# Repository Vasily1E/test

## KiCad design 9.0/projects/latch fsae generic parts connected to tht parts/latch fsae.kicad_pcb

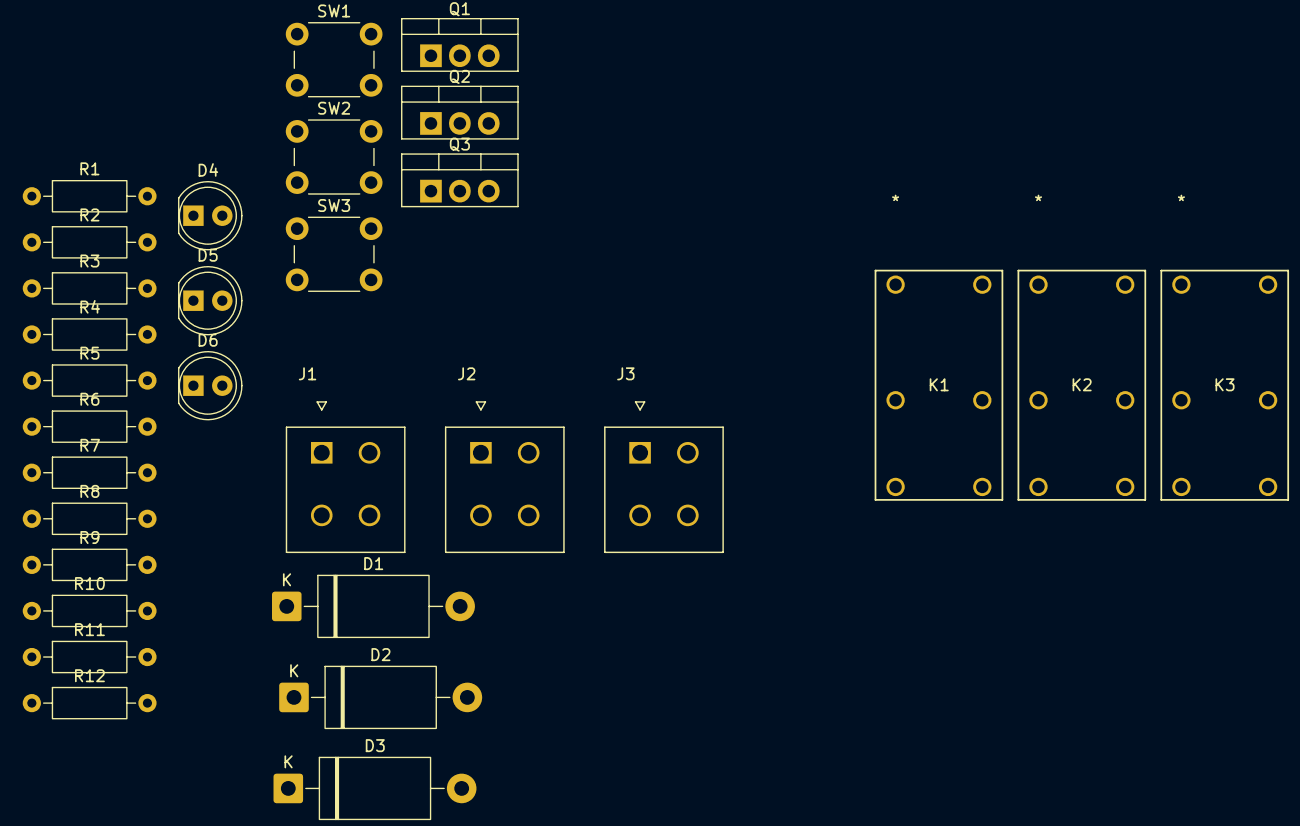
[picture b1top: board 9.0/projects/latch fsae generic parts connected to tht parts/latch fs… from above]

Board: 2 copper layers, 30 parts (0 on the bottom side), 20 nets, no tracks yet.

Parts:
D1, D2, D3: 1N4148WT; D_DO-201_P15.24mm_Horizontal
D4, D5, D6: DEBUG LED; LED_D5.0mm
J1, J2, J3: 2x2con; MOLEX_39296048
K1, K2, K3: Relay_DPST-NO; RELAY_G6B-2114P-US_OMR
Q1, Q2, Q3: PMOS; TO-220-3_Vertical
R1, R2, R3, R6, R8, R11: 1k; R_Axial_DIN0207_L6.3mm_D2.5mm_P10.16mm_Horizontal
R4, R7, R9: 470; R_Axial_DIN0207_L6.3mm_D2.5mm_P10.16mm_Horizontal
R5, R10, R12: 10k; R_Axial_DIN0207_L6.3mm_D2.5mm_P10.16mm_Horizontal
SW1, SW2, SW3: SW_Push; SW_PUSH_6mm

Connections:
+12V: J1.2, Q1.3 (S), Q2.3 (S), Q3.3 (S), SW1.1, SW3.1
BMS_FAULT: D3.2 (A), J2.4, R3.2
BSPD_FAULT: D1.2 (A), J2.1, R1.2
BSPDfault_LED: J3.2, R9.1
GND: D2.2 (A), J1.1, J3.1, R2.2, R5.2, R10.2, R12.2
GVLM_INPUT: J1.3, J1.4
IMD_FAULT: J2.3, SW2.1
IMDfault_LED: J3.4, R4.1, R7.1
unnamed: D1.1 (K), D4.2 (A), R5.1, R6.1, SW1.2
unnamed: D2.1 (K), D5.2 (A), R8.2, R10.1, SW2.2
unnamed: D3.1 (K), D6.2 (A), R11.2, R12.1, SW3.2
unnamed: D4.1 (K), R1.1
unnamed: D5.1 (K), R2.1
unnamed: D6.1 (K), R3.1
unnamed: Q1.1 (D), R7.2
unnamed: Q1.2 (G), R8.1
unnamed: Q2.1 (D), R9.2
unnamed: Q2.2 (G), R6.2
unnamed: Q3.1 (D), R4.2
unnamed: Q3.2 (G), R11.1

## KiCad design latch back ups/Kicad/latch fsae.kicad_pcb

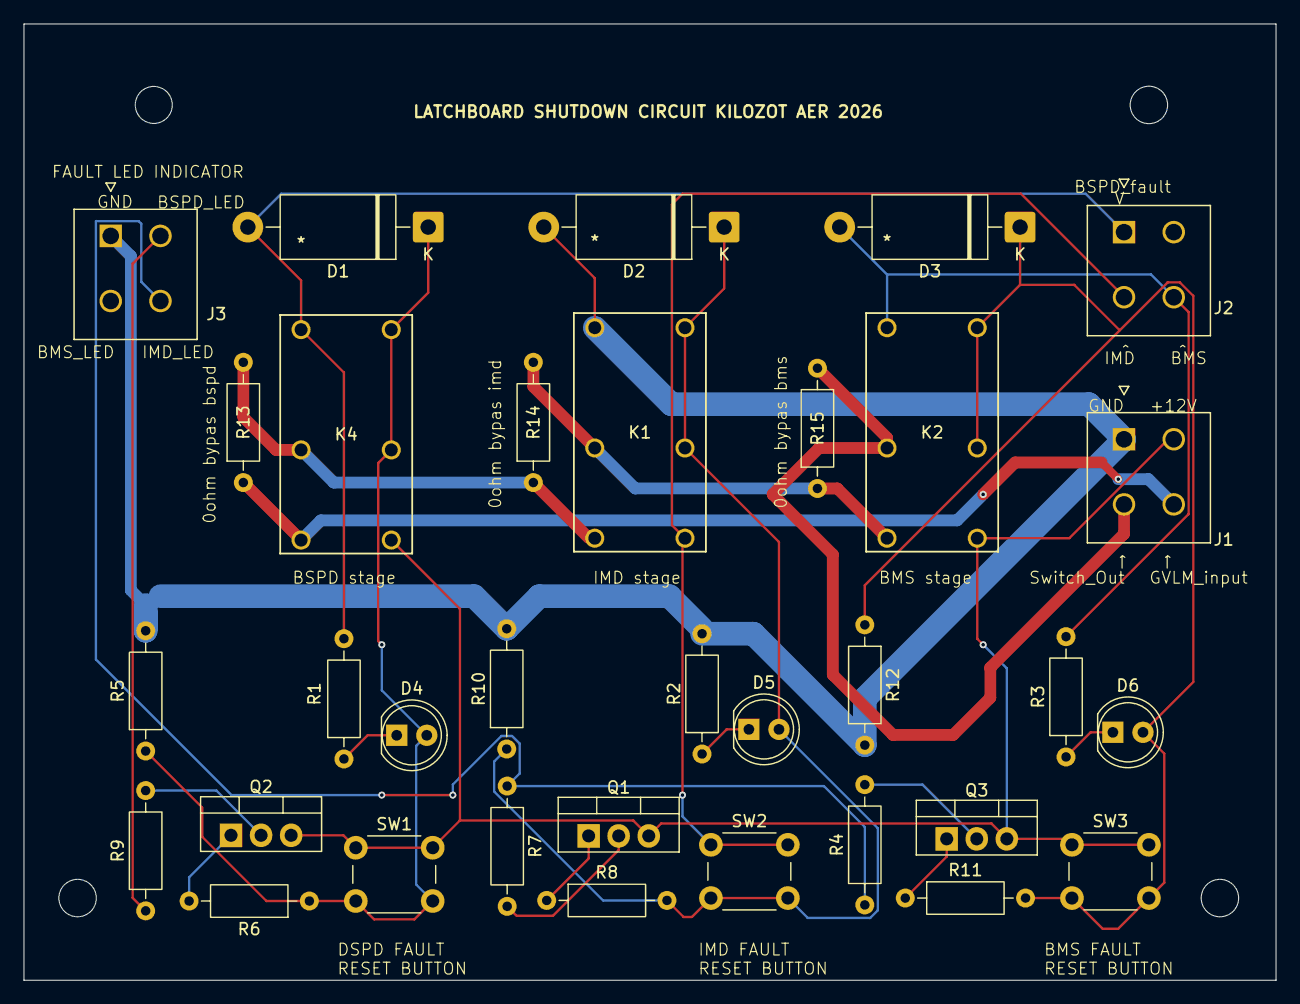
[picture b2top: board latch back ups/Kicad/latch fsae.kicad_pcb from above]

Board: 2 copper layers, 105.8 x 80.8 mm, 33 parts (0 on the bottom side), 23 nets.

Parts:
D1, D2, D3: 1N4148WT; D_DO-201_P15.24mm_Horizontal
D4, D5, D6: DEBUG LED; LED_D5.0mm
J1, J2, J3: 2x2con; MOLEX_39296048
K1, K2, K4: G6B-2214P-US DC12; RELAY_G6B-2114P-US_OMR
Q1, Q2, Q3: PMOS; TO-220-3_Vertical
R1, R2, R3, R6, R8, R11: 1k; R_Axial_DIN0207_L6.3mm_D2.5mm_P10.16mm_Horizontal
R4, R7, R9: 470; R_Axial_DIN0207_L6.3mm_D2.5mm_P10.16mm_Horizontal
R5, R10, R12: 10k; R_Axial_DIN0207_L6.3mm_D2.5mm_P10.16mm_Horizontal
R13, R14, R15: 0; R_Axial_DIN0207_L6.3mm_D2.5mm_P10.16mm_Horizontal
SW1, SW2, SW3: SW_Push; SW_PUSH_6mm

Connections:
+12V: J1.2, K2.5, K4.5, Q1.3 (S), Q2.3 (S), Q3.3 (S), SW1.1, SW3.1
BMS_FAULT: D3.2 (A), J2.4, K2.1, R3.2
BSPD_FAULT: D1.2 (A), J2.1, K4.1, R1.2
BSPDfault_LED: J3.2, R9.1
GND: D2.2 (A), J1.1, J3.1, K1.1, R2.2, R5.2, R10.2, R12.2
GVLM_INPUT: J1.4, K4.4, R13.1
IMD_FAULT: J2.3, K1.5, SW2.1
IMDfault_LED: J3.4, R4.1, R7.1
unnamed: D1.1 (K), D4.2 (A), K4.6, K4.8, R5.1, R6.1, SW1.2
unnamed: D2.1 (K), D5.2 (A), K1.6, K1.8, R8.2, R10.1, SW2.2
unnamed: D3.1 (K), D6.2 (A), K2.6, K2.8, R11.2, R12.1, SW3.2
unnamed: D4.1 (K), R1.1
unnamed: D5.1 (K), R2.1
unnamed: D6.1 (K), R3.1
unnamed: K1.3, K2.4, R14.2, R15.1
unnamed: K1.4, K4.3, R13.2, R14.1
unnamed: Q1.2 (D), R7.2
unnamed: Q1.1 (G), R8.1
unnamed: Q2.2 (D), R9.2
unnamed: Q2.1 (G), R6.2
unnamed: Q3.2 (D), R4.2
unnamed: Q3.1 (G), R11.1
internal_switch_output: J1.3, K2.3, R15.2

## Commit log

2026-01-15 Add .gitattributes and .gitignore.
2026-01-15 Add project files.
2026-01-15 Added latchboard
2026-01-15 Fixed embedded repo and added all PCB files
2026-01-15 Finalizing all files before force sync
